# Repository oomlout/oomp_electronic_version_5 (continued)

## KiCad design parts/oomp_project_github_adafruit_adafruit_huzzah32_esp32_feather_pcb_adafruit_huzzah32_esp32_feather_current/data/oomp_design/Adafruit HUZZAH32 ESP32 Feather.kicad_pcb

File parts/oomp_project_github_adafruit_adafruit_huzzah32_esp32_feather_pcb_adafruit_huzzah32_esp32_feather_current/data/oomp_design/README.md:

# OOMP KiCad design copy

Open `Adafruit HUZZAH32 ESP32 Feather.kicad_pro` (or the `.kicad_pcb` / `.kicad_sch`) in KiCad. Local OOMP libraries are under `libraries/`. Original inputs are preserved in [../original/](../original/).

Only verified unchanged installed KiCad defaults were renamed. Modified, custom, unmatched and unavailable items remain unchanged. Soldering variants are never swapped during conversion. Existing pad coordinates, nets and UUIDs are preserved.

See [conversion_report.yaml](conversion_report.yaml) for every conversion and skip. Copy this directory before editing; regeneration refuses to overwrite edited design files.

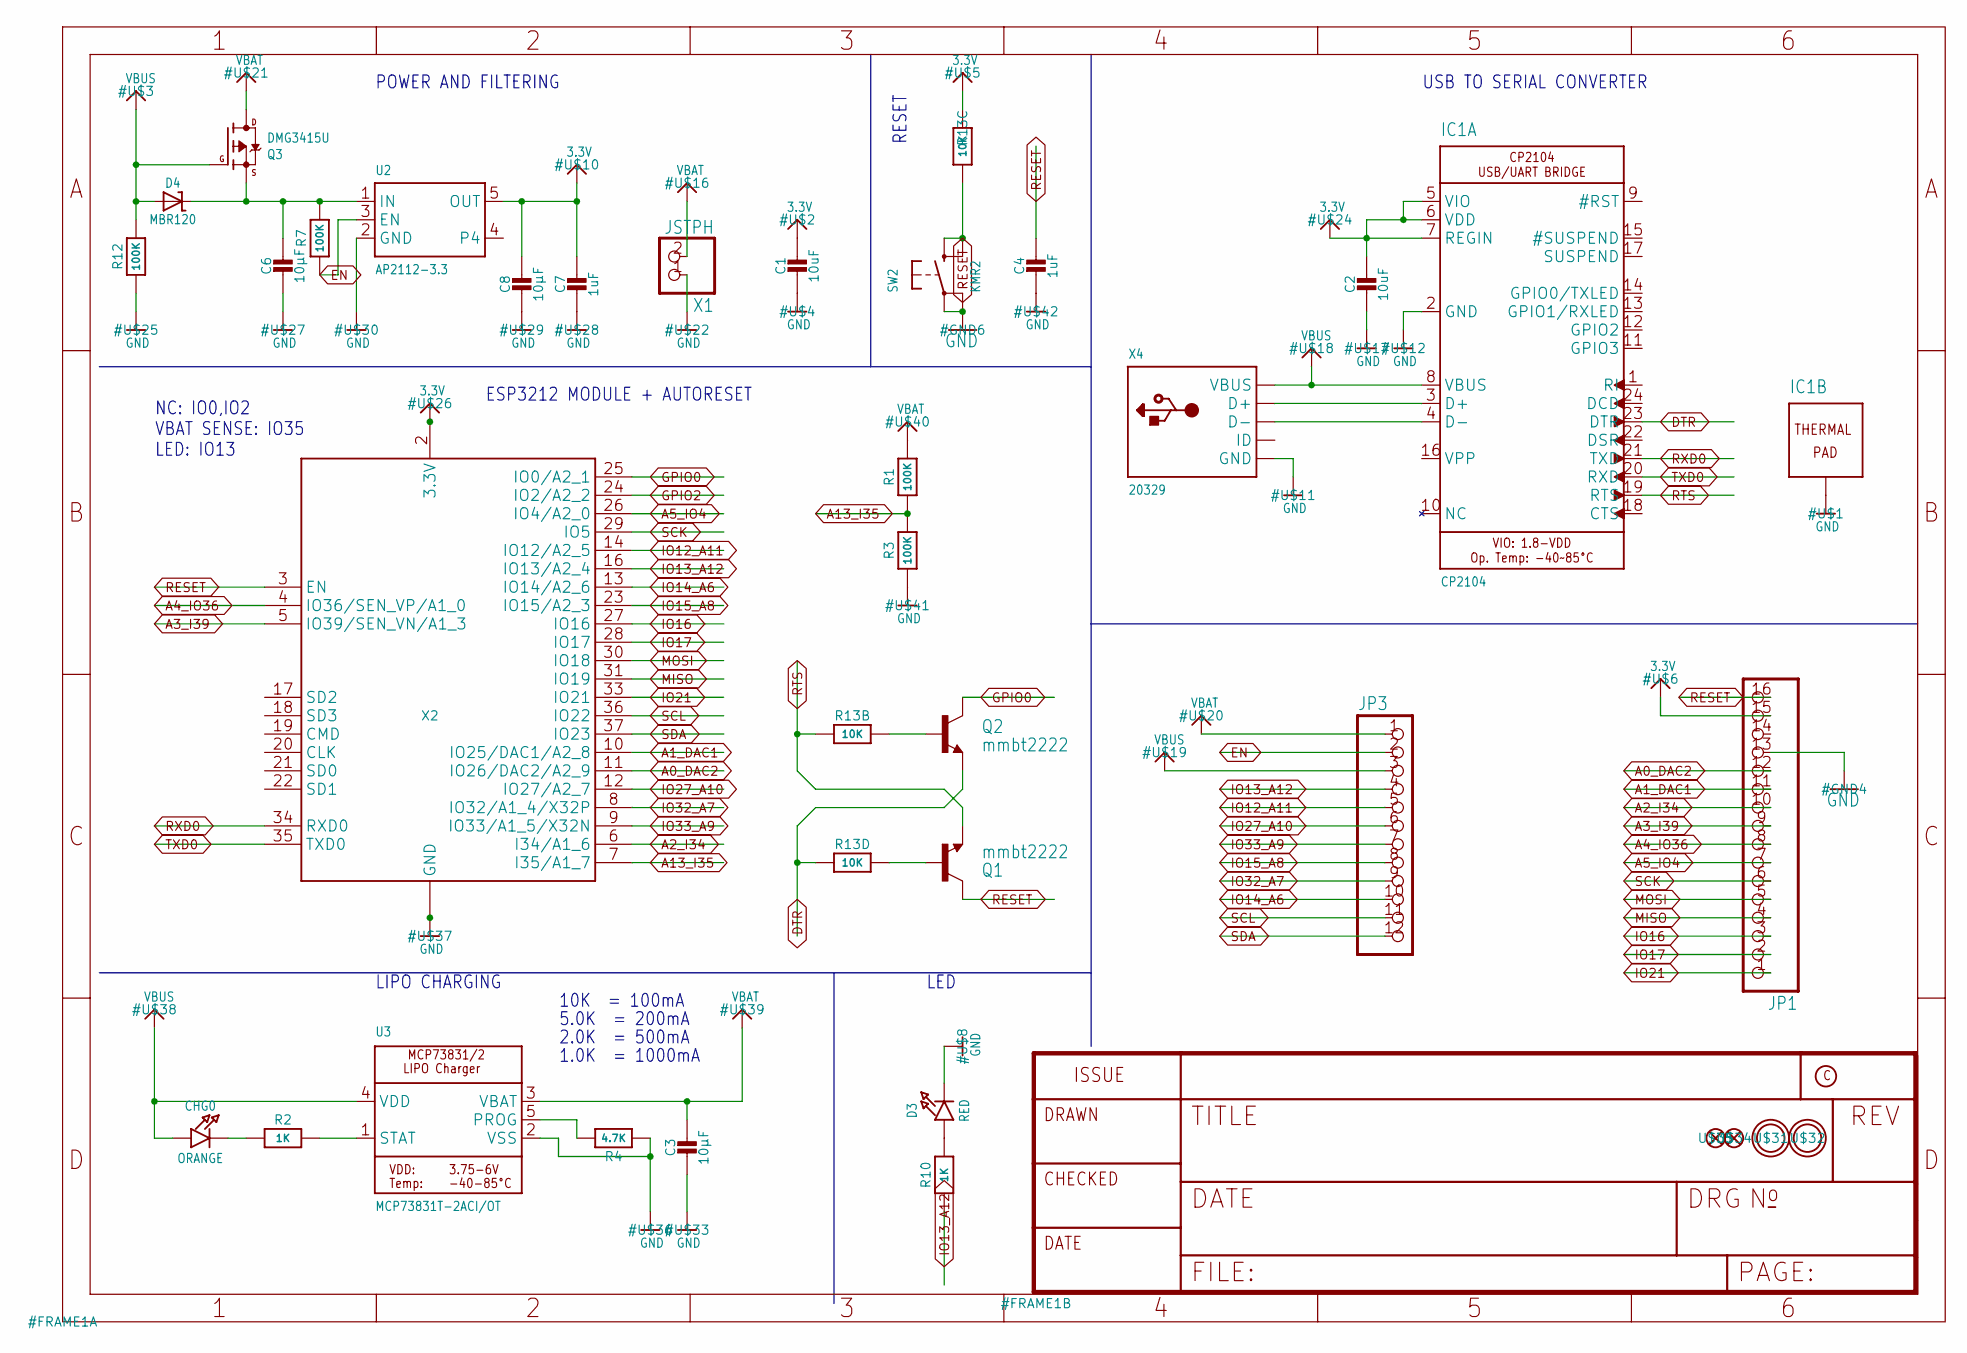
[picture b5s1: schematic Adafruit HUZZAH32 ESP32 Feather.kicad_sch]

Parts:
C1, C2: 10uF; 0805-NO
C3, C6, C8: 10µF; 0805-NO
C4, C7: 1uF; 0603-NO
CHG0: ORANGE; CHIPLED_0805_NOOUTLINE
D3: RED; CHIPLED_0805_NOOUTLINE
D4: MBR120; SOD-123
IC1: CP2104; QFN24_4MM_SMSC
JP1: HEADER-1X16_MIN; 1X16_ROUND_MIN
JP3: HEADER-1X12_MIN; 1X12_ROUND_MIN
Q1, Q2: mmbt2222; SOT23-3
Q3: DMG3415U; SOT23-R
R1, R3, R7, R12: 100K; 0603-NO
R2, R10: 1K; 0603-NO
R4: 4.7K; 0603-NO
R13: 10K; RESPACK_4X0603
SW2: KMR2; BTN_KMR2_4.6X2.8
U2: AP2112-3.3; SOT23-5
U3: MCP73831T-2ACI/OT; SOT23-5
U$31, U$32: MOUNTINGHOLE2.5; MOUNTINGHOLE_2.5_PLATED
U$34, U$35: FIDUCIAL_1MM
X1: JSTPH; JSTPH2
X2: ESP32_WROOM32_SKINNY; WROOM32_SKINNY
X4: 20329; 4UCONN_20329_V2

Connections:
3.3V: C1.1, C2.1, C7.1, C8.1, IC1.5 (VIO), IC1.6 (VDD), IC1.7 (REGIN), JP1.15, R13.3 (1), U2.5 (OUT), X2.2 (3.3V)
A0_DAC2: JP1.12, X2.11 (IO26/DAC2/A2_9)
A1_DAC1: JP1.11, X2.10 (IO25/DAC1/A2_8)
A2_I34: JP1.10, X2.6 (I34/A1_6)
A3_I39: JP1.9, X2.5 (IO39/SEN_VN/A1_3)
A4_IO36: JP1.8, X2.4 (IO36/SEN_VP/A1_0)
A5_IO4: JP1.7, X2.26 (IO4/A2_0)
A13_I35: R1.1, R3.2, X2.7 (I35/A1_7)
DTR: IC1.23 (DTR), Q2.2 (E), R13.4 (1)
EN: JP3.2, R7.1, U2.3 (EN)
GND: C1.2, C2.2, C3.2, C4.2, C6.2, C7.2, C8.2, D3.C, IC1.2 (GND), IC1.THERM (TP), JP1.13, R3.1, R4.1, R12.1, SW2.A, SW2.A' (P1), U2.2 (GND), U3.2 (VSS), X1.1, X2.1 (GND), X2.15 (GND), X2.38 (GND), X2.P$1 (GND), X4.BASE@1 (GND), X4.BASE@2 (GND), X4.GND, X4.SPRT@1 (GND), X4.SPRT@2 (GND), X4.SPRT@3 (GND), X4.SPRT@4 (GND)
GPIO0: Q2.3 (C), X2.25 (IO0/A2_1)
GPIO2: X2.24 (IO2/A2_2)
IO12_A11: JP3.5, X2.14 (IO12/A2_5)
IO13_A12: JP3.4, R10.1, X2.16 (IO13/A2_4)
IO14_A6: JP3.10, X2.13 (IO14/A2_6)
IO15_A8: JP3.8, X2.23 (IO15/A2_3)
IO16: JP1.3, X2.27 (IO16)
IO17: JP1.2, X2.28 (IO17)
IO21: JP1.1, X2.33 (IO21)
IO27_A10: JP3.6, X2.12 (IO27/A2_7)
IO32_A7: JP3.9, X2.8 (IO32/A1_4/X32P)
IO33_A9: JP3.7, X2.9 (IO33/A1_5/X32N)
MISO: JP1.4, X2.31 (IO19)
MOSI: JP1.5, X2.30 (IO18)
unnamed: CHG0.C, R2.1
unnamed: IC1.3 (D+), X4.D+
unnamed: R2.2, U3.1 (STAT)
unnamed: R4.2, U3.5 (PROG)
unnamed: D3.A, R10.2
unnamed: IC1.4 (D-), X4.D-
unnamed: C6.1, D4.C, Q3.2 (S), R7.2, U2.1 (IN)
unnamed: Q1.1 (B), R13.5 (2)
unnamed: Q2.1 (B), R13.2 (1)
RESET: C4.1, JP1.16, Q1.3 (C), R13.6 (2), SW2.B (S), SW2.B' (S1), X2.3 (EN)
RTS: IC1.19 (RTS), Q1.2 (E), R13.7 (2)
RXD0: IC1.21 (TXD), X2.34 (RXD0)
SCK: JP1.6, X2.29 (IO5)
SCL: JP3.11, X2.36 (IO22)
SDA: JP3.12, X2.37 (IO23)
TXD0: IC1.20 (RXD), X2.35 (TXD0)
VBAT: C3.1, JP3.1, Q3.3 (D), R1.2, U3.3 (VBAT), X1.2
VBUS: CHG0.A, D4.A, IC1.8 (VBUS), JP3.3, Q3.1 (G), R12.2, U3.4 (VDD), X4.VBUS

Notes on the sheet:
1.0K = 1000mA
10K = 100mA
NC: IO0,IO2 VBAT SENSE: IO35 LED: IO13
LED
2.0K = 500mA
POWER AND FILTERING
5.0K = 200mA
USB TO SERIAL CONVERTER
ESP3212 MODULE + AUTORESET
LIPO CHARGING
RESET

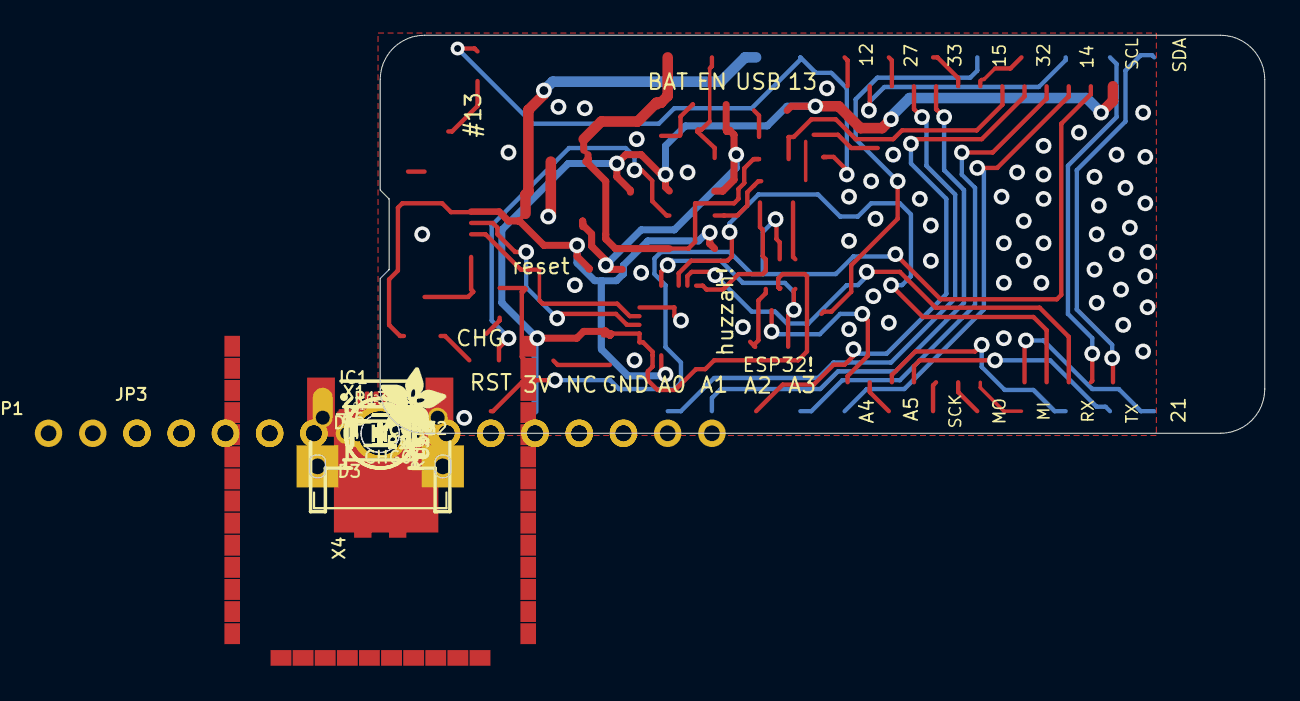
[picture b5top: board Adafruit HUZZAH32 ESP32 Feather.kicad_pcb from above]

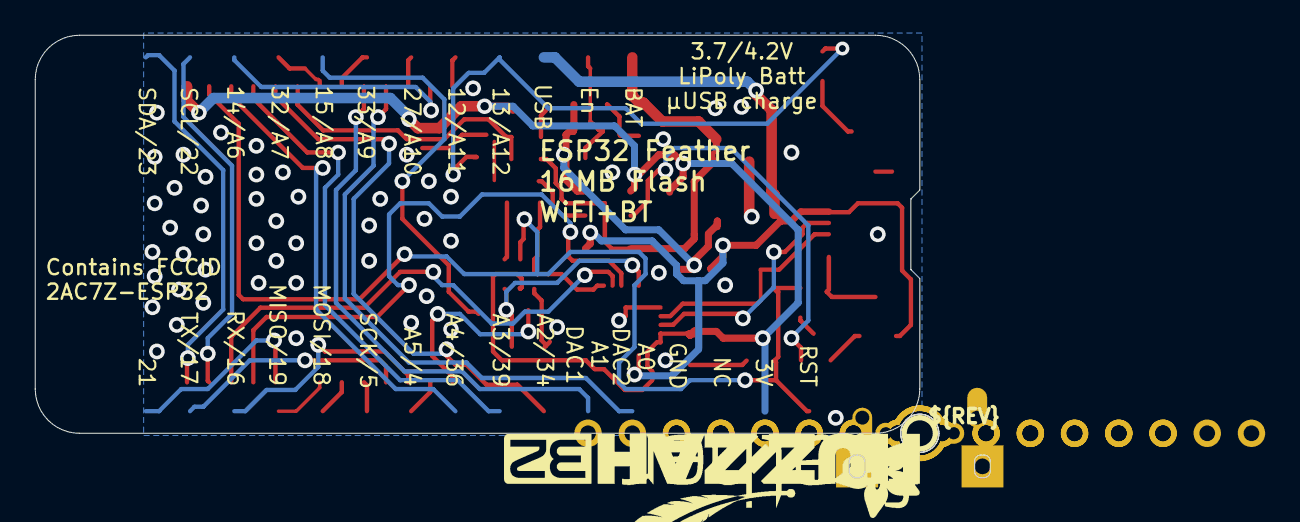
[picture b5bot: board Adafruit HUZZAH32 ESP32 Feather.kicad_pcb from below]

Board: 2 copper layers, 50.8 x 22.9 mm, 42 parts (4 on the bottom side), 42 nets.

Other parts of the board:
U$7: ADAFRUIT_5MM
U$9: FEATHERLOGO_MED
U$13: PCBFEAT-REV-040
U$14: ADAFRUIT_2.5MM
U$15: ADAFRUIT_3.5MM
U$43: HUZZAH32
UNK_HOLE_0: dummyfp0
UNK_HOLE_1: dummyfp1

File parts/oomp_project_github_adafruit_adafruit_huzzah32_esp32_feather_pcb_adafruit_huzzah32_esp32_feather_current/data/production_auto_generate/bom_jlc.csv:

Comment,Designator,Footprint,LCSC Part #
,JP3,Adafruit HUZZAH32 ESP32 Feather-import-fps:1X12_ROUND_MIN,C7501588
,JP1,Adafruit HUZZAH32 ESP32 Feather-import-fps:1X16_ROUND_MIN,C7501270
,U$14,Adafruit HUZZAH32 ESP32 Feather-import-fps:ADAFRUIT_2.5MM,
,U$15,Adafruit HUZZAH32 ESP32 Feather-import-fps:ADAFRUIT_3.5MM,
,U$7,Adafruit HUZZAH32 ESP32 Feather-import-fps:ADAFRUIT_5MM,
,U$9,Adafruit HUZZAH32 ESP32 Feather-import-fps:FEATHERLOGO_MED,
,U$43,Adafruit HUZZAH32 ESP32 Feather-import-fps:HUZZAH32,
,U$13,Adafruit HUZZAH32 ESP32 Feather-import-fps:PCBFEAT-REV-040,
100K,"R1,R3,R7,R12",Adafruit HUZZAH32 ESP32 Feather-import-fps:0603-NO,C25803
10K,R13,Adafruit HUZZAH32 ESP32 Feather-import-fps:RESPACK_4X0603,C98220
10uF,"C1,C2",Adafruit HUZZAH32 ESP32 Feather-import-fps:0805-NO,
10µF,"C3,C6,C8",Adafruit HUZZAH32 ESP32 Feather-import-fps:0805-NO,
1K,"R2,R10",Adafruit HUZZAH32 ESP32 Feather-import-fps:0603-NO,C2907002
1uF,"C4,C7",Adafruit HUZZAH32 ESP32 Feather-import-fps:0603-NO,C5673
20329,X4,Adafruit HUZZAH32 ESP32 Feather-import-fps:4UCONN_20329_V2,
4.7K,R4,Adafruit HUZZAH32 ESP32 Feather-import-fps:0603-NO,C23162
AP2112-3.3,U2,Adafruit HUZZAH32 ESP32 Feather-import-fps:SOT23-5,
CP2104,IC1,Adafruit HUZZAH32 ESP32 Feather-import-fps:QFN24_4MM_SMSC,
DMG3415U,Q3,Adafruit HUZZAH32 ESP32 Feather-import-fps:SOT23-R,
ESP32_WROOM32_SKINNY,X2,Adafruit HUZZAH32 ESP32 Feather-import-fps:WROOM32_SKINNY,
FIDUCIAL_1MM,"U$34,U$35",Adafruit HUZZAH32 ESP32 Feather-import-fps:FIDUCIAL_1MM,
JSTPH,X1,Adafruit HUZZAH32 ESP32 Feather-import-fps:JSTPH2,
KMR2,SW2,Adafruit HUZZAH32 ESP32 Feather-import-fps:BTN_KMR2_4.6X2.8,
MBR120,D4,Adafruit HUZZAH32 ESP32 Feather-import-fps:SOD-123,
MCP73831T-2ACI/OT,U3,Adafruit HUZZAH32 ESP32 Feather-import-fps:SOT23-5,
mmbt2222,"Q1,Q2",Adafruit HUZZAH32 ESP32 Feather-import-fps:SOT23-3,
ORANGE,CHG0,Adafruit HUZZAH32 ESP32 Feather-import-fps:CHIPLED_0805_NOOUTLINE,
RED,D3,Adafruit HUZZAH32 ESP32 Feather-import-fps:CHIPLED_0805_NOOUTLINE,
